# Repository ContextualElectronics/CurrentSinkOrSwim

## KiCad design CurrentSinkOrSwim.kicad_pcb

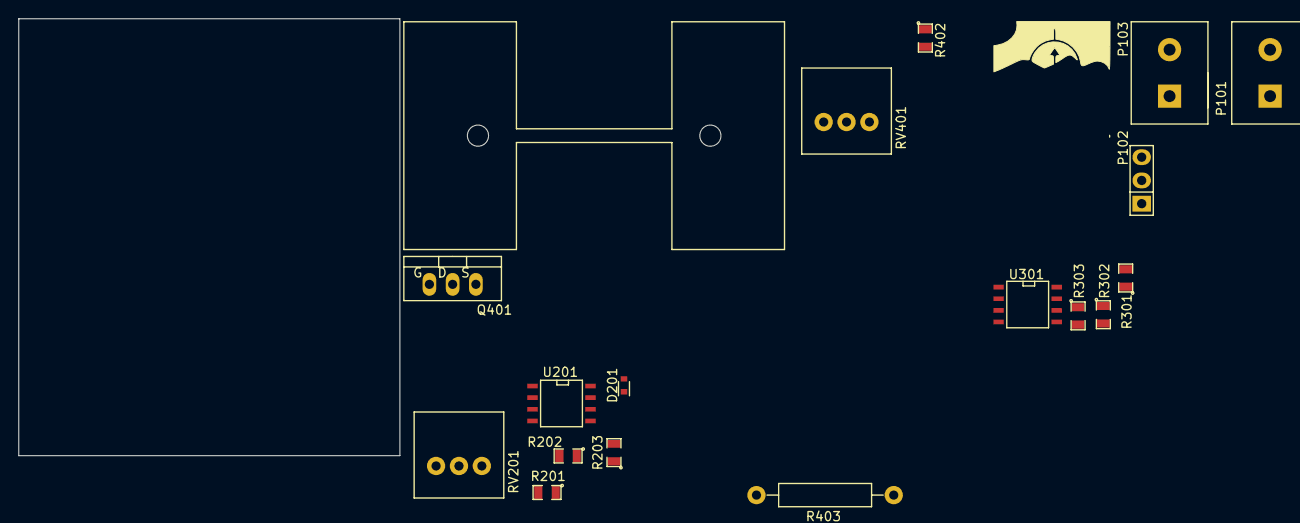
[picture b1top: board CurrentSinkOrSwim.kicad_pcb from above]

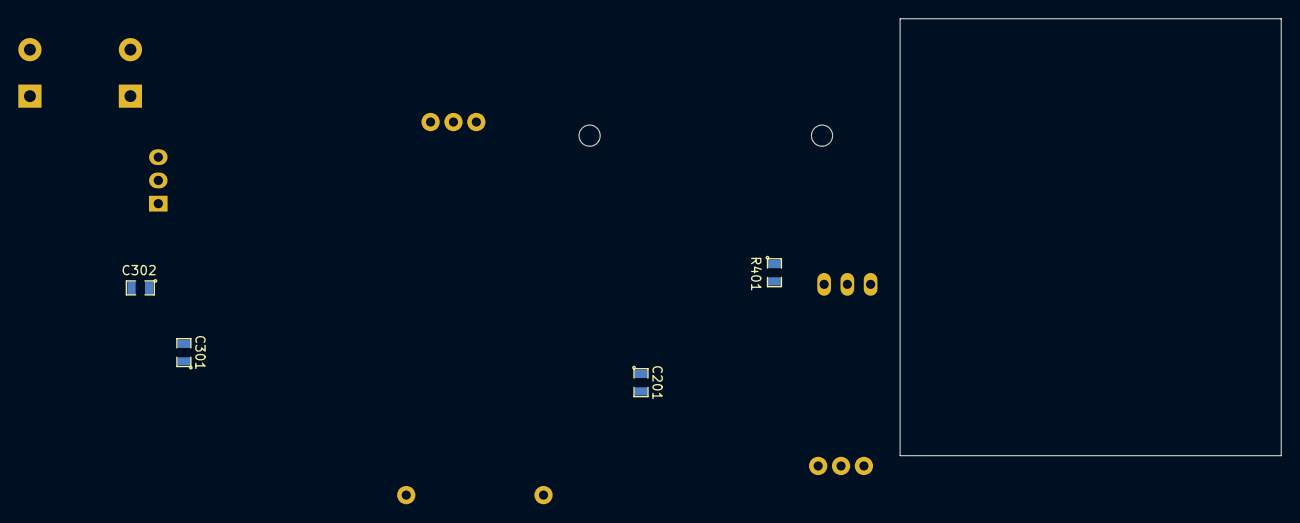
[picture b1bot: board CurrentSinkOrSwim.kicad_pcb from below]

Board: 2 copper layers, 41.7 x 47.8 mm, 22 parts (4 on the bottom side), 14 nets, no tracks yet.

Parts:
C201, C301, C302: C; SMD-0805
D201: DIODE; SOD-523
P1: CONN_01X01; FA-T220-38E
P101, P103: CONN_01X02; Terminal_Block_200_mil
P102: CONN_01X03; Pin_Header_Straight_1x03
Q401: BUK9575; TO-220_FET-GDS_Vertical
R201: 28.7K; SMD-0805
R202: 9K; SMD-0805
R203, R402: 1K; SMD-0805
R301: 0; SMD-0805
R302: 27K; SMD-0805
R303: 21.6K; SMD-0805
R401: 68K; SMD-0805
R403: .1; Resistor_Horizontal_RM15mm
RV201, RV401: 10K; P090L-02F25BR10K
U201: LMV358; SOIC-8-N
U301: LM2931D-R; SOIC-8-N

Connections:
2.7V: C201.1, C302.1, R201.1, R302.1, R401.1, U201.8, U301.1
/Current Control/Current_Sink+: P102.3, P103.1, Q401.D, R202.1
/Current Control/FET_Gate: D201.1, Q401.G, R402.1
/Power Regulation/Vin: C301.1, P102.2, U301.8
GND: C201.2, C301.2, C302.2, P101.2, P103.2, R203.2, R301.2, R303.2, R403.2, RV201.3, RV401.2, U201.4, U301.2, U301.3, U301.6, U301.7
unnamed: D201.2, U201.1
unnamed: P101.1, P102.1
unnamed: Q401.S, R403.1, U201.6
unnamed: R201.2, RV201.2, U201.3
unnamed: R202.2, R203.1, U201.2
unnamed: R301.1, U301.5
unnamed: R302.2, R303.1, U301.4
unnamed: R401.2, RV401.1, U201.5
unnamed: R402.2, U201.7

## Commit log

2015-03-03 Updated part numbers and generated BOM
2015-03-04 Updated BOM to group by reference
2016-02-25 Unknown changes before a Vagrant VM destroy
2017-11-04 Removed previous layout so now you can try it at home
